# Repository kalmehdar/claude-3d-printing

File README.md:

# Claude 3D printing

**Design, slice, print and fix 3D prints by talking to Claude.** Describe a part, or hand over an STL or a painted 3MF you
downloaded. Claude writes it in OpenSCAD with every size as a named number, exports one print file per colour, checks the
meshes, slices it for your printer and, if your printer runs Klipper, sends it, watches it layer by layer and tells you when
something goes wrong.

[**Live demo**](https://kalmehdar.github.io/claude-3d-printing/) · [Start in a minute](#start-in-a-minute) · [Set it up with your own Claude](#set-it-up-with-your-own-claude) · [Drive your printer](#drive-your-printer-from-the-claude-app) · [What to ask](#ask-claude) · [Add your own design](CONTRIBUTING.md)

| You want to | Use |
| --- | --- |
| Design a part and see it before printing | The `print-workflow` skill and the Print Bench page |
| Slice for your printer in plain words | `tools/orca.py` (`--preset figure`, `strong`, `fine-text`...) |
| Use a Bambu, Prusa, Creality or other printer | [docs/printers.md](docs/printers.md): build a slicer setup from the maker's profiles and hand the file over; only Klipper printers are driven directly |
| Print a painted multicolour model made for another printer | Workshop's 3MF import, which keeps the colours, supports and tower |
| Run and watch a Klipper printer from your phone or the Claude app | Workshop and the `printer` MCP server |
| Tune a filament without measuring anything | Numbered calibration tests: you tap the best piece |
| Fix a print that went wrong | The `print-troubleshooting` skill |
| Dry, store and track filament; finish, glue and paint a print; keep the printer maintained | The `filament-care`, `print-postprocess` and `print-maintenance` skills |
| Design the electronics inside a print | The `electronics-design`, `pcb-layout` and `enclosure-from-pcb` skills |

## Start in a minute

1. Install [Claude Code](https://claude.com/claude-code) and [OpenSCAD](https://openscad.org/downloads.html) (take a development snapshot: much faster).
2. In Claude Code, add this repo as a plugin marketplace and install the plugin:

   ```text
   /plugin marketplace add kalmehdar/claude-3d-printing
   /plugin install print-bench@print-bench
   ```

   That brings the skills, the agents and the tools in one go, and `/plugin` updates them later. (Prefer files? Clone the repo and copy `skills/` and `agents/` into `~/.claude/`.)

3. Restart Claude Code in an empty folder and ask: *"Design a Gridfinity bin, 2 x 1, 42 mm tall, for M3 screws, with the label printed in white. My printer is a Bambu A1 with the AMS."*

Claude asks anything it needs (your printer, caliper numbers for parts that must fit), then hands back the print files, a checked mesh, a Print Bench page and which file goes on which head.

## Set it up with your own Claude

Anyone can use this with their own Claude account; nothing here is tied to one person or one printer. The quickest way is to
let Claude do the setup. Open Claude Code in an empty folder and paste:

```text
Set up https://github.com/kalmehdar/claude-3d-printing for me. Install it as a Claude Code plugin
(/plugin marketplace add kalmehdar/claude-3d-printing, then /plugin install print-bench@print-bench),
or clone it and copy skills/ and agents/ into ~/.claude/ if plugins are off. Then run
python3 tools/c3dp.py doctor and install whatever it says is missing (OpenSCAD snapshot, OrcaSlicer,
Blender is optional). Ask me my printer model, nozzle size, plate and loaded filaments, and whether
it runs Klipper/Moonraker. If it does, set up Workshop and the printer MCP server as in the README.
Read docs/for-claude.md before doing anything else, and finish with a test-card slice for my printer.
```

Claude follows [docs/for-claude.md](docs/for-claude.md): what to install, the rules it keeps (no print starts without your
"the bed is clear" and a fresh camera picture, no fit size guessed, no profile changed without telling you), and a first job
to prove it works. Using the Claude desktop app instead of Claude Code? See [Design and slice from the Claude app](#design-and-slice-from-the-claude-app)
and [Drive your printer from the Claude app](#drive-your-printer-from-the-claude-app): two MCP servers, standard library only.

## Examples

Every example is on the [live demo](https://kalmehdar.github.io/claude-3d-printing/) in 3D, with its source, its STLs and a 3MF project that opens in Bambu Studio or OrcaSlicer with the colours already on their filaments.

| | | |
| --- | --- | --- |
|  |  |  |
| Four-colour test card | Colour-coded Gridfinity bins | Cable tags, each clip sized to its cable |
|  |  | |
| Filament swatch card with a see-through step strip | Desk cable clip, sized to your cable | |
|  |  | |
| Before: a plain downloaded STL | After: Claude added a label, a red rim and magnet pockets | |

These pictures come from `tools/render.py`, from the same files you can download.

## What's here

| Path | What it does |
| --- | --- |
| `tools/c3dp.py` | One command for all of it: `c3dp doctor` checks what is installed, `c3dp look`, `export`, `slice`, `fit`, `printer`, `spools`, `mcp design`; `c3dp setup` puts it on your PATH |
| `tools/design_mcp.py` | Design-and-slice tools for the Claude desktop app and Claude Code (an MCP server, standard library only): save and read OpenSCAD designs, a four-view picture, export colour parts, slice with presets and named settings, a mesh check (Blender), fits, a colour 3MF project, open in OrcaSlicer, Spoolman stock |
| `tools/look.py` | One picture with four views (angled, top, front, side) of an OpenSCAD design in its colours, plus its real size in mm, so Claude checks the shape before exporting |
| `tools/export_parts.py` | Exports each colour part of an OpenSCAD model to its own STL and checks it fits your bed |
| `tools/mesh_audit.py` | Runs inside Blender: non-manifold edges, inside-out meshes, pieces, thin walls, bed fit, and printability notes: steep overhang area and the longest bridge, with the fix |
| `tools/param_sets.py` | Named size sets beside a design (`model.json`, the file OpenSCAD's Customizer reads): Cat6 or USB for the cable clip, 1x1 or 2x2 for a bin. `check --render` builds every set |
| `tools/fit.py` | Your printer's measured fits (slide and press clearance from the fit card, the M3 heat-set insert hole from the insert card, the print-in-place hinge gap from the hinge card), so every design uses them instead of a material guess |
| `tools/orca.py` | Drives OrcaSlicer in plain words: `slice part.stl --printer u1 --preset strong --set infill=30 supports=on` gives time and grams; presets draft, standard, strong, solid, fine, quality, polished, lean, low-waste; `open` shows the result in the app; `add-material` and `install` put your printer, filaments and presets in the app's menus ; `new-printer` builds a printer setup from a slicer's vendor profiles and `adopt-gcode` takes the start/end G-code from a known-good print |
| `tools/slice_stats.py` | Slices every bench design with OrcaSlicer's command line and records real print time and grams per printer in `slice-stats.json`; the bench shows them with a printer switch |
| `tools/printer_mcp.py` | Printer tools for the Claude desktop app and Claude Code (an MCP server, standard library only): status, camera picture, layer photos from past and overnight prints, designs, slice and send, start (needs the person's "bed is empty"), pause, resume, cancel, queue, unload, set filament, light, history, warnings, activity. Each person runs it in their own Claude app against Workshop, so their own Claude account does the work and the activity log shows their name. Setup in the file's docstring |
| `tools/printer.py` | Drives a Klipper/Moonraker printer from the command line: status with loaded filament, camera frame, send, start only after `--bed-clear`, queue, pause/cancel, light, and `watch` (a camera frame per layer until the job ends). The `print-workflow` skill uses it to send, start, watch and log prints |
| `tools/workshop.py` | Workshop: one page (phone, tablet, desktop) to watch a Klipper/Moonraker printer and its camera, run its job queue, keep a photo of every layer and a timelapse of each print (30 days), preview any G-code toolpath in 3D before printing, browse every bench design in 3D and slice it with `orca.py` straight onto the printer. `python tools/workshop.py --printer <address>`; home network or VPN only |
| `tools/install-mac.sh` | Installs or updates OrcaSlicer, Snapmaker Orca, the OpenSCAD snapshot and Blender on a Mac with Homebrew (`--alpha` adds Snapmaker Orca's newest pre-release) |
| `tools/print_bench.py` | Builds the Print Bench page from a `bench.json`: one HTML file with the 3D viewer, size lines, a measure tool and download links |
| `tools/make_3mf.py` | Packs a design's per-colour STLs into one 3MF project that Bambu Studio and OrcaSlicer open with every part on its filament and the colours set |
| `tools/render.py` | Runs inside Blender: a studio picture of every design in its print colours, or all of them in one line-up (`--lineup`), for READMEs and posts |
| `.github/workflows/pages.yml` | Rebuilds the Print Bench page and publishes it on GitHub Pages on every push |
| `examples/models/` | Five designs (a four-colour test card, colour-coded Gridfinity bins, clip-on cable tags sized per cable, a filament swatch card, a desk cable clip) and `upgrade-bin.scad`, which upgrades an existing STL |
| `examples/before/` | The plain STL that `upgrade-bin.scad` starts from |
| `examples/stl/`, `examples/bench.json` | Their exported parts and the demo page's list |
| `skills/` | Claude Code skills: `print-workflow` (drives these tools from idea or STL to checked, previewed print files), `electronics-design`, `pcb-layout` and `enclosure-from-pcb` (circuits to boards to cases), `3d-print-designer` (FDM design rules, verification, and material guides for PLA, PETG, ABS, ASA, TPU, nylon and carbon-fibre fills), `print-calibration`, `print-troubleshooting`, `filament-care` (drying, storage, Spoolman), `print-postprocess` (supports, sanding, painting, annealing, gluing, inserts), `print-maintenance` (intervals, plate care) plus `modeling`, `blender`, `blender-3d-modeling`, `texturing`, `asset-optimization`, `animation`, `rigging`, `unity`, `vroid`, `omniverse` |
| `tools/pcb.py` and friends | Circuit to orderable PCB: ERC, KiCad board from code, autorouting, DRC, JLCPCB files, 3D models (`pcb_kicad.py`, `kicad_env.py`, `trace_width.py`) |
| `hardware/` | Electronics projects, each with specs, circuit, board, fab files and a printed case. First one: `hardware/led-bar` |
| `agents/` | Seven 3D subagents (analyst, modeler, texturer, rigger, animator, asset optimiser, VTuber specialist) |

## Drive your printer from the Claude app

Talk to your printer the way you talk to Claude: "what's printing?", "slice the cable clip in black and queue it", "the bed's clear, start it", "unload T2".

1. Run Workshop next to your Klipper/Moonraker printer (`python tools/workshop.py --printer <address>`), on a home network or a VPN.
2. In the Claude desktop app: Settings, Developer, Edit Config, and add
   `{"mcpServers": {"printer": {"command": "python3", "args": ["<repo>/tools/printer_mcp.py"], "env": {"WORKSHOP_URL": "http://<workshop>:8090", "WORKSHOP_USER": "<your name>"}}}}`, then restart the app.
   In Claude Code: `claude mcp add printer -e WORKSHOP_URL=http://<workshop>:8090 -e WORKSHOP_USER=<your name> -- python3 <repo>/tools/printer_mcp.py`.
3. Each person uses their own Claude account; every action goes through Workshop's checks (no start without "the bed is empty", none while a head is unloaded or the bed would be cold) and shows in its activity log under their name.

## Design and slice from the Claude app

Ask for a part in the Claude desktop app ("a wall hook for a 20 mm rail, in black PETG, strong") and Claude writes the OpenSCAD
design, shows you four views, exports the parts and slices them for your printer, with time and grams.

1. Install OpenSCAD and OrcaSlicer (see Full setup), then check with `python tools/c3dp.py doctor`.
   Installed this repo as a Claude Code plugin? Both servers (`design` and `printer`) come with it: Claude Code asks for the
   Python command (`python` on Windows), your designs folder and, if you have them, Spoolman and Workshop addresses. Skip step 2.
2. In the Claude desktop app: Settings, Developer, Edit Config, and add
   `{"mcpServers": {"design": {"command": "python3", "args": ["<repo>/tools/design_mcp.py"], "env": {"DESIGN_DIR": "<a folder for your designs>"}}}}`, then restart the app.
   In Claude Code: `claude mcp add design -e DESIGN_DIR=<folder> -- python3 <repo>/tools/design_mcp.py`. On Windows the command is `python`.
3. Designs are written only inside that folder. Add `"SPOOLMAN_URL": "http://<spoolman>:7912"` to `env` and every slice says
   whether a spool has enough left.

Running a Snapmaker U1? Read [docs/snapmaker-u1.md](docs/snapmaker-u1.md) first.

## Full setup

1. Install [OpenSCAD](https://openscad.org/downloads.html). Take a development snapshot: it renders with the manifold backend, seconds instead of minutes.
2. Install [Blender](https://www.blender.org/download/) for the mesh check (optional, but it catches problems early).
3. Install your printer maker's slicer (Bambu Studio, OrcaSlicer, PrusaSlicer, Snapmaker Orca).
4. Optional: [BOSL2](https://github.com/BelfrySCAD/BOSL2) in OpenSCAD's library folder, for print-in-place hinges (`examples/models/hinge-card.scad`) and other ready-made parts.
5. Install the plugin as in [Start in a minute](#start-in-a-minute), or copy `skills/` and `agents/` into `~/.claude/`.

## Ask Claude

With the skills installed, open Claude Code in a folder where you want the files and ask in plain words. The `print-workflow` skill runs the tools for you: model, export, mesh check, Print Bench, and a short hand-over with which file goes on which head.

- "Design a Gridfinity bin, 2 x 1, 42 mm tall, for M3 screws, with the label printed in white. My printer is a Bambu A1 with the AMS."
- "Here's an STL I downloaded. Add a printed-in label on the front and magnet pockets in the base."
- "This phone stand is 2 mm too tight for my case. The case measures 11.4 mm. Fix the slot."
- "Make this part print in two colours: the top 3 mm in red."
- "Show me everything I've designed so far on a Print Bench, with renders for my README."
- "I want a USB-C powered board with an ESP32 and 16 addressable LEDs for my rack, running WLED. Spec it, design the PCB and a case."

Give Claude caliper numbers for anything that has to fit. It never guesses a fit size; it marks those `FIT` and asks.

## Hardware: circuits, boards and the case around them

| | |
| --- | --- |
|  |  |
| A board Claude specced, laid out, routed and checked | The same board on the printed faceplate built from its numbers |

Claude can design the electronics too, as far as an order-ready board, and then a printed case that fits the board exactly. The worked example is the [rack status LED bar](hardware/led-bar): an ESP32-C3 and 16 addressable LEDs behind a 1U faceplate, running WLED.

The steps, each a skill:

1. **`electronics-design`**: requirements, a specs sheet, a power budget, parts checked against their datasheets (never from memory), protection, then the circuit written as Python with [SKiDL](https://github.com/devbisme/skidl) and an electrical rules check.
2. **`pcb-layout`**: `python tools/pcb.py all hardware/<name>` builds the KiCad board from that code, places the parts from a layout file, autoroutes with Freerouting, pours ground, runs KiCad's design-rules check and writes Gerbers, a BOM and a placement file in JLCPCB's format, plus STEP and STL models.
3. **`enclosure-from-pcb`**: the board's outline, holes and parts heights go into OpenSCAD (`pcb.py dims`), the case is designed around them, and the Print Bench shows the board inside it.

**An autorouted board from Claude is a first pass, not something to order blind.** Every project has a REVIEW.md that a person works through in KiCad before ordering, and Claude never places an order. The DRC passing proves the rules were met, not that the circuit is right.

Extra setup for hardware: [KiCad 10](https://www.kicad.org/download/), Java 25 ([Temurin](https://adoptium.net/)) and the [Freerouting](https://github.com/freerouting/freerouting/releases) jar in `~/.local/share/freerouting/`, then `pip install skidl schemdraw`. No mains voltage: the skills stop at low-voltage DC and say so.

## Try it

```bash
cd claude-3d-printing/examples
python ../tools/export_parts.py models/test-card.scad --out stl --bed 256x256x256
blender --background --factory-startup --python ../tools/mesh_audit.py -- stl --bed 256
python ../tools/print_bench.py bench.json print-bench.html
```

Open `print-bench.html` in a browser. For pictures:

```bash
blender --background --factory-startup --python ../tools/render.py -- bench.json renders
```

 To share it, fork this repo, set Settings, Pages, Source to "GitHub Actions", and point the `download` URL in `bench.json` at your fork: every push rebuilds your page.

Set `OPENSCAD` to the binary if it isn't on your PATH. A model lists its colour parts on its first line (`// parts: red blue white black`); each becomes `<model>-<part>.stl`. In the slicer, load all of a model's parts as one object and give each part its own head.

## Upgrade a print you already have

Most prints start as someone else's STL. Claude can improve one without the original source file: OpenSCAD's `import()` loads the STL as a solid, and three operations do the rest. `difference()` cuts into it, `union()` adds to it, `intersection()` pulls a region out so it can print in another colour. `examples/models/upgrade-bin.scad` does all three to a plain bin in about 30 lines. In the demo, compare "before" and "after".

Things to ask for:

| Upgrade | How Claude does it |
| --- | --- |
| A label printed into it | A 0.6 mm text pocket cut into a face; the same text, clipped to the part, becomes a second-colour STL that fills it |
| A second colour on a part that has one | `intersection()` with a slab or shape takes that region out as its own STL; `difference()` removes it from the body |
| A better fit | Grow or shrink a hole by cutting a new cylinder through it; `resize()` or `scale()` in one axis for a part that is a few percent off |
| Magnets, screws, heat-set inserts | Pockets cut at measured positions (magnet size plus 0.2 mm clearance) |
| Mount it somewhere | `union()` a hook, a Skadis peg, a screw tab or a Gridfinity foot onto it |
| Stronger | Fill a thin wall, or add a rib along the part that snapped |
| Too big for your bed | Cut it into pieces with `intersection()`, and add a dovetail or alignment pins at the joint |
| Broken mesh | Run `mesh_audit.py`. If it is non-manifold, re-export it from Blender's 3D Print Toolbox, or have Claude rebuild the part in OpenSCAD from measurements |

How to ask: give Claude the STL, say what is wrong with it or what you want added, and give caliper numbers for anything it has to fit. Claude reads the STL's size and bounds first (`export_parts.py` and `mesh_audit.py` both print them), writes the upgrade with each position as a named number, exports the parts, audits them, and adds a before and after to your Print Bench. For bigger changes it is often cleaner to have Claude redraw the part in OpenSCAD from measurements, which makes every later change one number.

Check the licence first. Many models on Printables, MakerWorld and Thingiverse allow remixes for personal use only (CC BY-NC); credit the original in anything you share.

## The way I work with Claude

- Ask for a part with its job and its numbers. "A bin for 10 USB sticks, 42 mm Gridfinity grid, label USB printed into the front."
- Never let Claude guess a fit size. Anything that clips onto, slides into or screws to something real needs a caliper number. Claude marks those `FIT` and you measure before printing.
- Labels are printed in, not stuck on. A 0.6 mm pocket in the body, the letters in a second colour filling it, printed face down.
- One colour per head, one STL per colour. The `part` variable picks which colour a run of OpenSCAD draws.
- Check before slicing. `mesh_audit.py` must say 0 files need a fix. Squares that touch only at a corner are the usual non-manifold culprit; overlap them by 0.01 mm.
- Look at it first. Rebuild the Print Bench and turn the model round on your phone before you print.

## First-week tips

From DIY WISCO's [10 Things I Wish I Knew Before I Started 3D Printing](https://youtu.be/fetbc62jeWI), in my words, plus what four colours taught us:

- Start with PLA. PETG when it needs to take heat; ABS and ASA want an enclosure and real ventilation.
- Use the slicer's own profiles. The maker's slicer, your printer, your filament, default settings, until a few prints succeed.
- A print that won't stick usually means a dirty plate. Wash it with dish soap and warm water, dry it fully, hold it by the edges. Glue stick if that fails.
- Watch the first layer, then walk away. Even lines that are stuck down mean the rest will probably go fine. Check on it by camera if you have one.
- Dry your filament. Popping at the nozzle, sudden stringing or a rough surface mean wet filament. PETG soaks it up faster than PLA, and new sealed spools can still be wet.
- Supports only where needed. Tree supports come off more easily.
- The time estimate is a guide. Expect it to run over.
- For models, try MakerWorld, Printables, Thingiverse. Pick ones with photos of real prints.
- For several colours, print the test card first. A four-colour plate needs room for the prime tower, so a set that fills the bed splits into two plates.

## Licence

The tools and example designs are MIT (see `LICENSE`). Each skill and the agents keep their own licence, in their folder; `SOURCES.md` lists where each came from.

More of my Claude Code setup: [claude-kit](https://github.com/kalmehdar/claude-kit).

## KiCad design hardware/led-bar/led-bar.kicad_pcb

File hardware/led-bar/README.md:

# Rack status LED bar

A 1U panel for a 10-inch rack: 16 addressable LEDs and an ESP32-C3 on one board, behind a printed faceplate with a white diffuser window. Powered and flashed over one USB-C cable, and runs [WLED](https://kno.wled.ge/), so it's controlled from a phone or Home Assistant.

Designed end to end with Claude Code: the specs, the circuit, the board layout, the routing, the checks, the order files and the faceplate. **Not built yet.** Before ordering, a person works through [REVIEW.md](REVIEW.md).

| File | What it is |
| --- | --- |
| [SPECS.md](SPECS.md) | What it does, the power budget, every part with its datasheet and LCSC number |
| [overview.svg](overview.svg) | The circuit as blocks: power along the top, data below |
| `circuit.py` | The circuit as code (SKiDL). Its electrical rules check passes with 0 errors |
| `layout.py`, `board.json` | Where every part sits, the board rules and the power track widths |
| `led-bar.kicad_pcb`, `led-bar.kicad_pro` | The KiCad board: open it in KiCad 10 to look or change things |
| `fab/` | Ready to order: `led-bar-gerbers.zip`, `led-bar-bom-jlcpcb.csv`, `led-bar-cpl-jlcpcb.csv`, plus STEP and STL models and renders |
| `case.scad`, `stl/` | The printed 1U faceplate and diffuser, built from the board's own numbers (`board_dims.scad`) |
| [REVIEW.md](REVIEW.md) | The checklist a person ticks before ordering |

## Rebuild it

Needs KiCad 10, Java 25 and [Freerouting](https://github.com/freerouting/freerouting/releases) (see the main README).

```bash
python tools/pcb.py all hardware/led-bar
```

That runs the circuit's rules check, places the parts, autoroutes, runs KiCad's design-rules check (last run: 0 errors, 0 unconnected, 0 warnings), writes every fab file and the case dimensions. Then export the faceplate:

```bash
python tools/export_parts.py hardware/led-bar/case.scad --out hardware/led-bar/stl --bed 270x270x270
```

The faceplate is 254 mm wide, so it needs a printer bed of 255 mm or more.

## Order and build

1. Work through REVIEW.md in KiCad.
2. Upload `fab/led-bar-gerbers.zip` to JLCPCB (2 layers, 1.6 mm), choose top-side assembly, then upload the BOM and CPL files. All the parts are in JLCPCB's stock list; the passives are Basic parts.
3. Print the faceplate face down: `case-panel` in black PETG, `case-diffuser` in white PETG on a second head. Fix the board to the standoffs with four M3 x 6 self-tapping screws.
4. Plug in USB-C, open [install.wled.me](https://install.wled.me) in Chrome or Edge, and flash WLED.
5. In WLED: LED Preferences, data GPIO **4**, 16 LEDs, type WS281x. Set the brightness limiter to **400 mA** on a laptop USB port, or **1100 mA** on a 2 A or better USB-C charger (the fuse runs warm in a rack, so stay under it).

## What Claude got wrong on the way (kept so the skills learn)

- SKiDL calls its no-connect net `__NOCONNECT`; the board builder first treated it as a real net and joined every unused pin together. Caught by reading the DRC, fixed in `tools/pcb_kicad.py`.
- KiCad 7 and later keep net classes in the project file. Until the builder wrote `.kicad_pro`, the router never saw the wide power tracks.
- The first module choice (ESP32-C3-MINI-1) is marked not recommended for new designs and has no KiCad library footprint; the board uses the WROOM-02 instead.

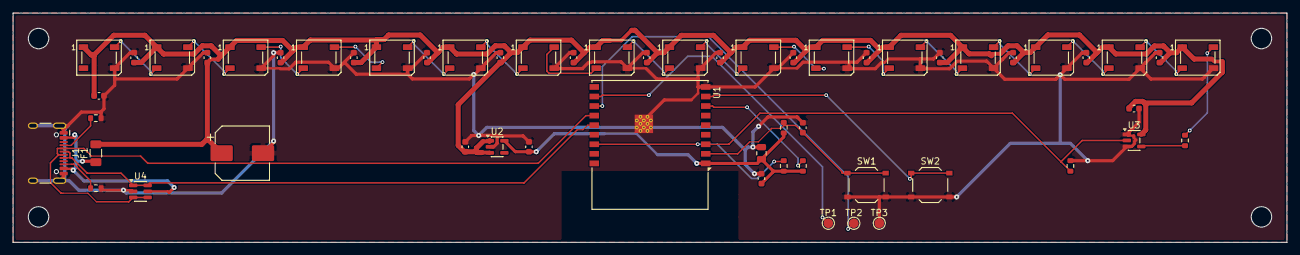
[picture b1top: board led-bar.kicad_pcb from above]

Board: 2 copper layers, 200.0 x 36.0 mm, 61 parts (0 on the bottom side), 32 nets.

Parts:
C1: 470uF 16V; CP_Elec_8x10
C2, C3, C6: 1uF; C_0603_1608Metric
C4: 10uF; C_0805_2012Metric
C5, C7, C8, C9, C10, C11, C12, C13, C14, C15, C16, C17, C18, C19, C20, C21, C22, C23: 100nF; C_0603_1608Metric
D1, D2, D3, D4, D5, D6, D7, D8, D9, D10, D11, D12, D13, D14, D15, D16: WS2812B; LED_WS2812B_PLCC4_5.0x5.0mm_P3.2mm
F1: 1.5A hold; Fuse_1206_3216Metric
H1, H2, H3, H4: M3; MountingHole_3.2mm_M3
J1: USB-C; USB_C_Receptacle_HCTL_HC-TYPE-C-16P-01A
R1, R2: 5.1k; R_0603_1608Metric
R3, R4, R5, R7: 10k; R_0603_1608Metric
R6: 390; R_0603_1608Metric
SW1: RESET; SW_Push_1P1T_XKB_TS-1187A
SW2: BOOT; SW_Push_1P1T_XKB_TS-1187A
TP1: RXD; TestPoint_Pad_D1.5mm
TP2: TXD; TestPoint_Pad_D1.5mm
TP3: GND; TestPoint_Pad_D1.5mm
U1: ESP32-C3-WROOM-02-N4; ESP32-C3-WROOM-02
U2: AP2112K-3.3; SOT-23-5
U3: 74AHCT1G125; SOT-23-5
U4: USBLC6-2SC6; SOT-23-6

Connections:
+3V3: C3.1, C4.1, C5.1, R3.1, R4.1, R5.1, U1.1, U2.5
+5V: C1.1, C2.1, C7.1, C8.1, C9.1, C10.1, C11.1, C12.1, C13.1, C14.1, C15.1, C16.1, C17.1, C18.1, C19.1, C20.1, C21.1, C22.1, C23.1, D1.1, D2.1, D3.1, D4.1, D5.1, D6.1, D7.1, D8.1, D9.1, D10.1, D11.1, D12.1, D13.1, D14.1, D15.1, D16.1, F1.2, U2.1, U2.3, U3.5
BOOT: SW2.1, U1.8
EN: C6.1, R3.2, SW1.1, U1.2
GND: C1.2, C2.2, C3.2, C4.2, C5.2, C6.2, C7.2, C8.2, C9.2, C10.2, C11.2, C12.2, C13.2, C14.2, C15.2, C16.2, C17.2, C18.2, C19.2, C20.2, C21.2, C22.2, C23.2, D1.3, D2.3, D3.3, D4.3, D5.3, D6.3, D7.3, D8.3, D9.3, D10.3, D11.3, D12.3, D13.3, D14.3, D15.3, D16.3, J1.A1, J1.A12, J1.B1, J1.B12, J1.SH, R1.2, R2.2, R7.2, SW1.2, SW2.2, TP3.1, U1.9, U1.19, U2.2, U3.1, U3.3, U4.2
LED_CHAIN_1: D1.2, D2.4
LED_CHAIN_2: D2.2, D3.4
LED_CHAIN_3: D3.2, D4.4
LED_CHAIN_4: D4.2, D5.4
LED_CHAIN_5: D5.2, D6.4
LED_CHAIN_6: D6.2, D7.4
LED_CHAIN_7: D7.2, D8.4
LED_CHAIN_8: D8.2, D9.4
LED_CHAIN_9: D9.2, D10.4
LED_CHAIN_10: D10.2, D11.4
LED_CHAIN_11: D11.2, D12.4
LED_CHAIN_12: D12.2, D13.4
LED_CHAIN_13: D13.2, D14.4
LED_CHAIN_14: D14.2, D15.4
LED_CHAIN_15: D15.2, D16.4
LED_DATA_3V3: R7.1, U1.3, U3.2
LED_DATA_5V: D1.4, R6.2
unnamed: J1.A5, R1.1
unnamed: J1.B5, R2.1
unnamed: R4.2, U1.16
unnamed: R5.2, U1.7
unnamed: R6.1, U3.4
RXD: TP1.1, U1.11
TXD: TP2.1, U1.12
USB_DM: J1.A7, J1.B7, U1.13, U4.3, U4.4
USB_DP: J1.A6, J1.B6, U1.14, U4.1, U4.6
VBUS: F1.1, J1.A4, J1.A9, J1.B4, J1.B9, U4.5

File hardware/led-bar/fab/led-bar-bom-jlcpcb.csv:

Comment,Designator,Footprint,LCSC Part #
1.5A hold,F1,Fuse_1206_3216Metric,C20802
100nF,"C5,C7,C8,C9,C10,C11,C12,C13,C14,C15,C16,C17,C18,C19,C20,C21,C22,C23",C_0603_1608Metric,C14663
10k,"R3,R4,R5,R7",R_0603_1608Metric,C25804
10uF,C4,C_0805_2012Metric,C15850
1uF,"C2,C3,C6",C_0603_1608Metric,C15849
390,R6,R_0603_1608Metric,C23151
470uF 16V,C1,CP_Elec_8x10,C165531
5.1k,"R1,R2",R_0603_1608Metric,C23186
74AHCT1G125,U3,SOT-23-5,C7484
AP2112K-3.3,U2,SOT-23-5,C51118
BOOT,SW2,SW_Push_1P1T_XKB_TS-1187A,C318884
ESP32-C3-WROOM-02-N4,U1,ESP32-C3-WROOM-02,C2934560
RESET,SW1,SW_Push_1P1T_XKB_TS-1187A,C318884
USB-C,J1,USB_C_Receptacle_HCTL_HC-TYPE-C-16P-01A,C2894897
USBLC6-2SC6,U4,SOT-23-6,C7519
WS2812B,"D1,D2,D3,D4,D5,D6,D7,D8,D9,D10,D11,D12,D13,D14,D15,D16",LED_WS2812B_PLCC4_5.0x5.0mm_P3.2mm,C2761795

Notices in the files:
README.md:
MIT licence
